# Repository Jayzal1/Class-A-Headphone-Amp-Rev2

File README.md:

# Class-A-Headphone-Amp-Rev2
Class A Headphone Amp Rev2

This is a design for a class A headphone amplifier with a case for mounting under a desk. It's pure analogue with phono rca input and a passthrough output which trigger when the amplifier is switch off. There is a built in linear pwoer supply running from a standard IEC Socket on the back panel. There are two front panel switches, left one is for power and the right one was intended to disable a 12v trigger option that was never implemented. The case is capable of being fully 3D printed. The case was built around an old headsink I had spare so if anyone would like to build this a redesign might be required to fit others. All the M3 panel screws are designed to run into [brass inserts]([url](https://www.google.com/search?q=m3+brass+inserts&rlz=1C1ONGR_en-gbGB988GB988&oq=m3+brass+inserts&gs_lcrp=EgZjaHJvbWUyCQgAEEUYORiABDIHCAEQABiABDIICAIQABgHGB4yCAgDEAAYBRgeMg0IBBAAGIYDGIAEGIoFMg0IBRAAGIYDGIAEGIoFMg0IBhAAGIYDGIAEGIoFMg0IBxAAGIYDGIAEGIoFMgoICBAAGIAEGKIEMgoICRAAGIAEGKIE0gEINzgwMWowajSoAgCwAgE&sourceid=chrome&ie=UTF-8)) which get melted into the 3D printed case.

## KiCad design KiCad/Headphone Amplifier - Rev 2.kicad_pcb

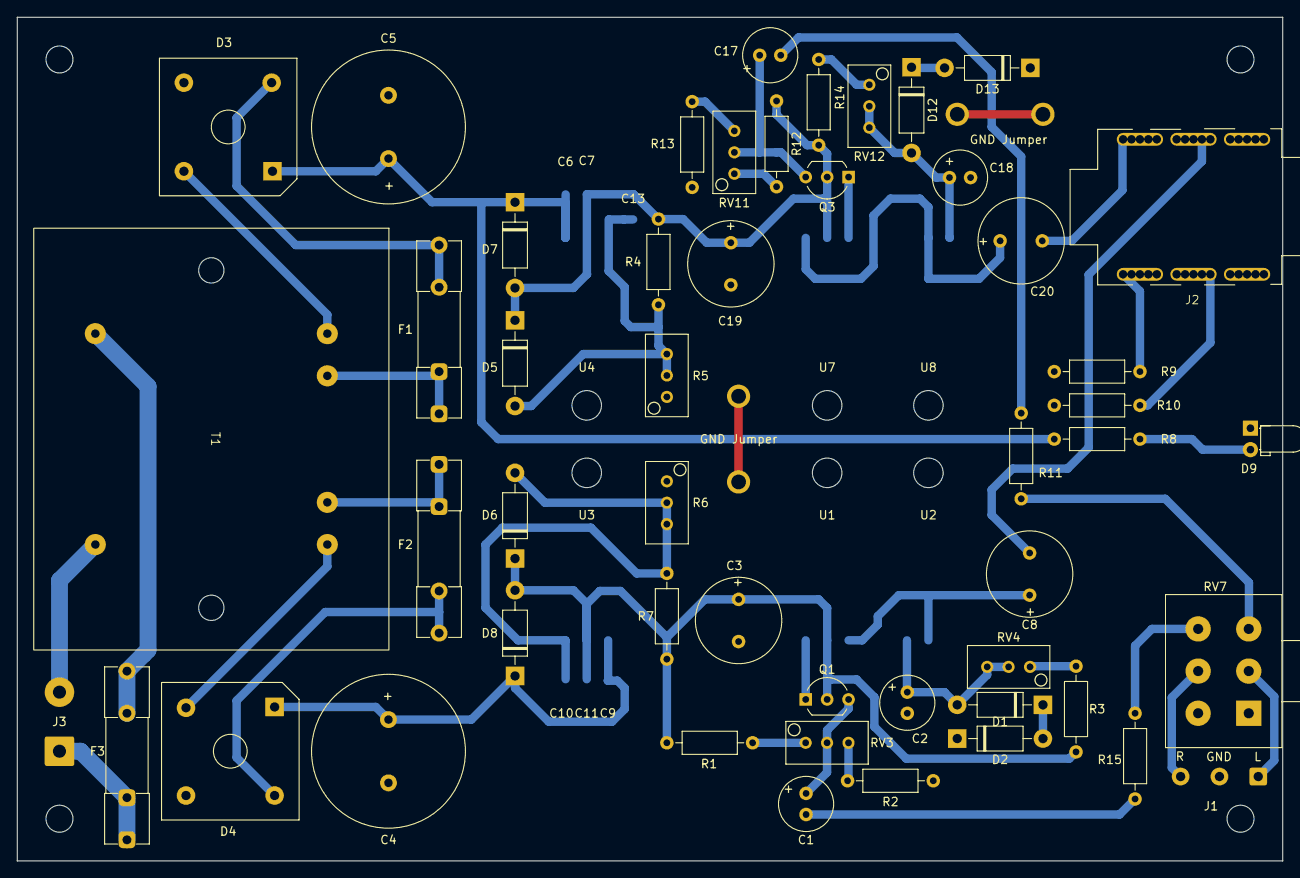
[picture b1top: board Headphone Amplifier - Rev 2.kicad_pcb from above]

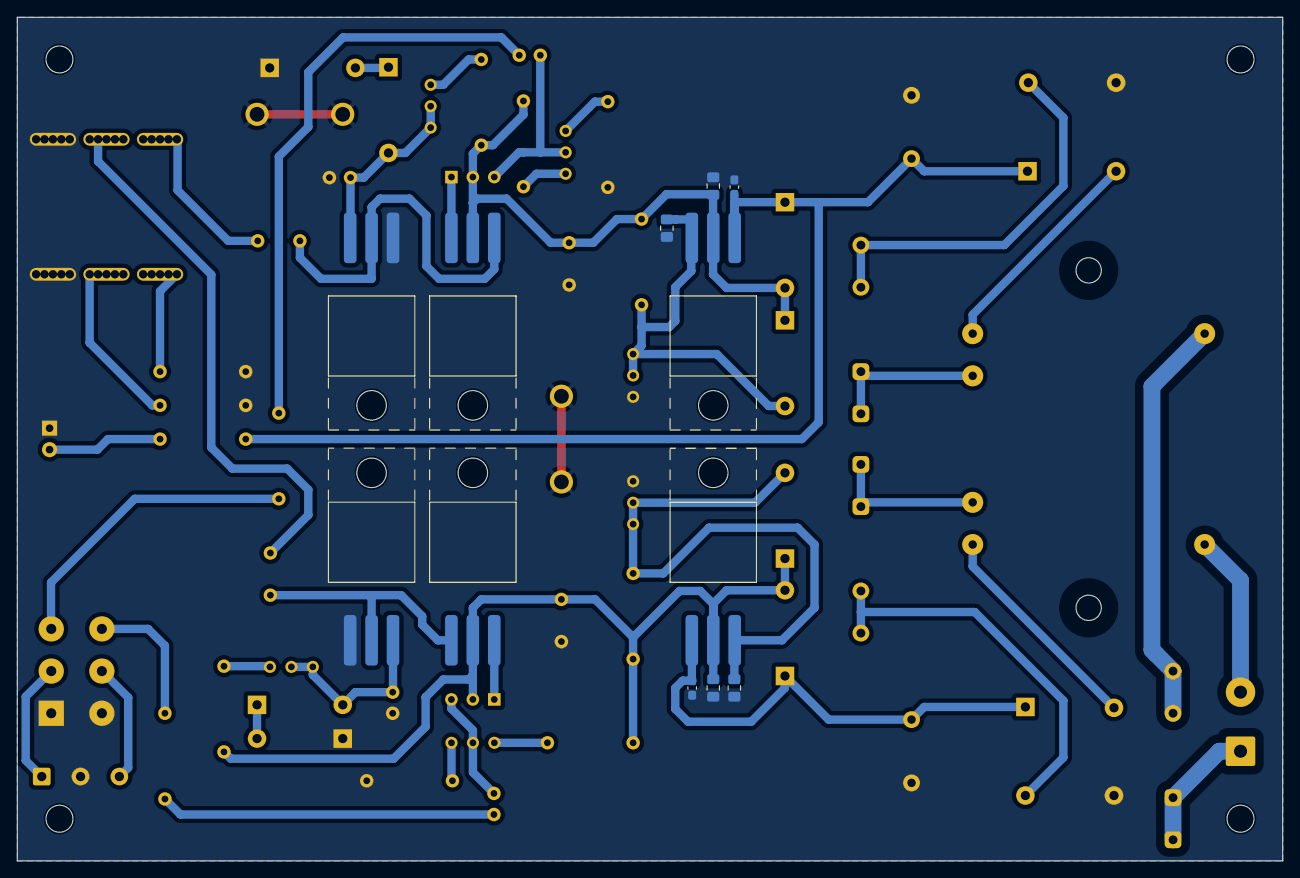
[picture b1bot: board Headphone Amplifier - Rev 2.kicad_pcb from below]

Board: 2 copper layers, 150.0 x 100.0 mm, 64 parts (12 on the bottom side), 43 nets.

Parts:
C1, C2, C17, C18: 33uF; C_Radial_D6.3mm_H11.0mm_P2.50mm
C3, C8, C19, C20: 470uF; C_Radial_D10.0mm_H12.5mm_P5.00mm
C4, C5: 4700uF; Nichicon 4700uF, 35v, 85c - D18.0mm_H35.5mm_P7.50mm
C6, C9: 0.1uF; C_0603_1608Metric_Pad1.08x0.95mm_HandSolder
C7, C11: 1uF; C_0805_2012Metric_Pad1.18x1.45mm_HandSolder
C10, C13: 22uF; C_0805_2012Metric_Pad1.18x1.45mm_HandSolder
D1, D2, D12, D13: 1N4001; D_DO-41_SOD81_P10.16mm_Horizontal
D3: L Rectifier; Diode_Bridge_Vishay_KBPC1
D4: R Rectifier; Diode_Bridge_Vishay_KBPC1
D5, D6, D7, D8: 1N4002; D_DO-41_SOD81_P10.16mm_Horizontal
D9: PWR_LED; FrontPanel_LED_D3.0mm_Horizontal_O1.27mm_Z6.0mm
F1, F2, F3: Fuse; Amazon_Fuseholder-5x20mm_Littelfuse_111_Inline_P20.00x5.00m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
GND Jumper: SolderWire-1sqmm_1x02_P5.4mm_D1.4mm_OD2.7mm
GND Jumper#2: SolderWire-1sqmm_1x02_P5.4mm_D1.4mm_OD2.7mm
J1: Signal In; SolderWire-0.5sqmm_1x03_P4.6mm_D0.9mm_OD2.1mm
J2: Signal Output; NMJ6HC-S
J3: Mains Input; SolderWire-0.75sqmm_1x02_P7mm_D1.25mm_OD3.5mm
Q1, Q3: 2SC1815; TO-92_Inline_Wide
R1, R2, R12, R13: 10K; Resistor_Axial_0.25W_L6.3mm_D2.5mm_P10.16mm
R3, R14: 15K; Resistor_Axial_0.25W_L6.3mm_D2.5mm_P10.16mm
R4, R7: R220; Resistor_Axial_0.25W_L6.3mm_D2.5mm_P10.16mm
R5, R6: 5K; Potentiometer_Bourns_3296W_Vertical
R8: 2K; Resistor_Axial_0.25W_L6.3mm_D2.5mm_P10.16mm
R9, R10: 1K; Resistor_Axial_0.25W_L6.3mm_D2.5mm_P10.16mm
R11, R15: 1R; Resistor_Axial_0.25W_L6.3mm_D2.5mm_P10.16mm
RV3, RV4, RV11, RV12: 10K; Potentiometer_Bourns_3296W_Vertical
RV7: Dual 100K Vol Pot; Dual_Potentiometer_Horizontal
T1: Myrra_41176_15v_10VA_Transformer; Myrra_44274_15v_10VA_Transformer
U1, U2, U7, U8: TIP31C; TO-220-3_Horizontal_TabUp_FlatLegs
U3, U4: LM317; TO-220-3_Horizontal_TabUp_FlatLegs

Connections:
/Left Amplifier Channel/15V: C7.1, C19.1, D5.1 (K), D7.2 (A), Q3.2 (C), R4.2, R12.1, R14.1, U4.2 (VO), U7.2
/Left Amplifier Channel/Signal Input: R11.1, RV7.3
/Left Amplifier Channel/Signal Output: C20.2, J2.T
/Power Supply/17.3v AC: D3.4, T1.12
/Power Supply/22.9v: C5.1, C6.1, D3.1 (+), D7.1 (K), R8.2, U4.3 (VI)
/Power Supply/+15V (R): C3.1, C11.1, D6.1 (K), D8.2 (A), Q1.2 (C), R1.1, R3.1, R7.2, U1.2, U3.2 (VO)
/Right Amplifier Channel/Signal Input: R15.1, RV7.6
/Right Amplifier Channel/Signal Output: C8.2, J2.R
GND: C2.2, C3.2, C4.2, C5.2, C6.2, C7.2, C9.2, C10.2, C11.2, C13.2, C18.2, C19.2, D2.1 (K), D3.3 (-), D4.3 (-), D9.1 (K), D13.1 (K), GND Jumper.1, GND Jumper.2, GND Jumper#2.1, GND Jumper#2.2, J1.2, J2.S, J2.SN, R2.2, R5.1, R6.1, R9.2, R10.2, R13.2, RV7.1, RV7.4, U2.3, U8.3
unnamed: C1.2, R15.2
unnamed: C8.1, U1.3, U2.2
unnamed: C17.2, R11.2
unnamed: C20.1, U7.3, U8.2
unnamed: C2.1, D1.2 (A), RV4.2, RV4.3, U2.1
unnamed: D1.1 (K), D2.2 (A)
unnamed: D3.2, F1.2
unnamed: C4.1, C9.1, D4.1 (+), D8.1 (K), U3.3 (VI)
unnamed: D4.2, T1.7
unnamed: D4.4, F2.2
unnamed: C13.1, D5.2 (A), R4.1, R5.2, R5.3, U4.1 (ADJ)
unnamed: C10.1, D6.2 (A), R6.2, R6.3, R7.1, U3.1 (ADJ)
unnamed: D9.2 (A), R8.1
unnamed: C18.1, D12.2 (A), RV12.2, RV12.3, U8.1
unnamed: D12.1 (K), D13.2 (A)
unnamed: F1.1, T1.11
unnamed: F2.1, T1.8
unnamed: F3.2, T1.1
unnamed: J1.1, RV7.2
unnamed: J1.3, RV7.5
unnamed: J2.RN, R10.1
unnamed: J2.TN, R9.1
unnamed: F3.1, J3.1
unnamed: J3.2, T1.6
unnamed: C1.1, Q1.3 (B), RV3.2
unnamed: Q1.1 (E), U1.1
unnamed: C17.1, Q3.3 (B), RV11.2
unnamed: Q3.1 (E), U7.1
unnamed: R1.2, RV3.1
unnamed: R2.1, RV3.3
unnamed: R3.2, RV4.1
unnamed: R12.2, RV11.1
unnamed: R13.1, RV11.3
unnamed: R14.2, RV12.1

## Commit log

2024-09-08 Create delete
